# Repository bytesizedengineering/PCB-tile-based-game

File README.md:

# PCB Tile Based Board Game 

*Whoever completes the longest path wins! But beware of collisions!*  

## 🚀 Overview  
When Zach is not knee-deep in circuits and code, you can probably find him around a table covered in board games. For a long time now, a little project has been brewing in the back of his mind, designing a board game from the ground up, but not just any board game. Zach wants to create a tile-based game where the tiles electronically interact with each other the moment they snap together. It was featured on the Digkey [YouTube channel](https://www.youtube.com/@digikey) in [this video](https://youtu.be/TUmDfVxSnFg?si=vBeNglg9jUsEn66M).  

## 📂 Repository Structure  
```
📁 mechanical_design/   # 3D models (Fusion 360, STLs, STEP files)
📁 electrical_design/   # KiCad PCB and schematic files
📁 firmware/            # Arduino, ESP, or other firmware code
📁 docs/                # PDFs, images, and additional documentation
```

## 🔩 Mechanical Design  
You can access the latest Fusion 360 model here:  
[🔗 View 3D Model in Fusion 360](https://a360.co/4kI0F6f)

## 🏗️ Build Instructions  

### 🖨️ 3D Printing  
- **Recommended Material**: PLA/PETG  
- **Layer Height**: 0.2mm  
- **Supports**: No  

### 🔌 Electronics  
- **Microcontroller**: ATTiny3217  
- **Power Supply**: 5V  
- **PCB Fabrication**: Gerber files included in `electrical_design/` 

### 💾 Firmware Upload  
You can upload code to the ATtiny3217 using the [Adafruit UPDI Friend](https://learn.adafruit.com/adafruit-updi-friend). Here's a quick setup guide for the Arduino IDE:

🧰 What You Need
- Adafruit UPDI Friend
- Arduino IDE
- ATtiny3217 board
- USB-C cable
1. Install MegaTinyCore
2. Select the Board
3. Connect the UPDI Friend
4. Select the Serial Port
5. Upload Code

## 🛒 Bill of Materials (BOM)  
| Part            | Description                                 | Purchase Link                                     |
| --------------- | ------------------------------------------- | ------------------------------------------------- |
| Microcontroller | ATtiny3217                                  | [DigiKey](https://www.digikey.com/short/wtvwb0pv) |
| Connector       | Magnetic Connector Pair                     | [DigiKey](https://www.digikey.com/short/tv5t94mz) |
| Capacitor       | 0.1 µF Ceramic Capacitor                    |                                                   |
| LED             | Addressable Reverse-Mount RGB LED           | [DigiKey](https://www.digikey.com/short/zhvb3bff) |
| PCB             | Custom-designed                             |                                                   |

## 🎥 Video & More Info  
📺 Watch the full build video: [YouTube Video](https://youtu.be/TUmDfVxSnFg?si=vBeNglg9jUsEn66M)  

## 📝 License  
This project is licensed under the **GNU General Public License v3.0**.  
You can read the full text in the [`LICENSE`](LICENSE) file or at [gnu.org](https://www.gnu.org/licenses/gpl-3.0.html).  

## ❤️ Support  
- Found this helpful? Consider supporting me on [Patreon](https://www.patreon.com/ByteSizedEngineering) or [YouTube Memberships](https://www.youtube.com/@ByteSizedEngineering/join).  
- Follow me on [YouTube](https://www.youtube.com/@ByteSizedEngineering), [Instagram](https://www.instagram.com/bytesizedengineering/), and [GitHub](https://github.com/bytesizedengineering).

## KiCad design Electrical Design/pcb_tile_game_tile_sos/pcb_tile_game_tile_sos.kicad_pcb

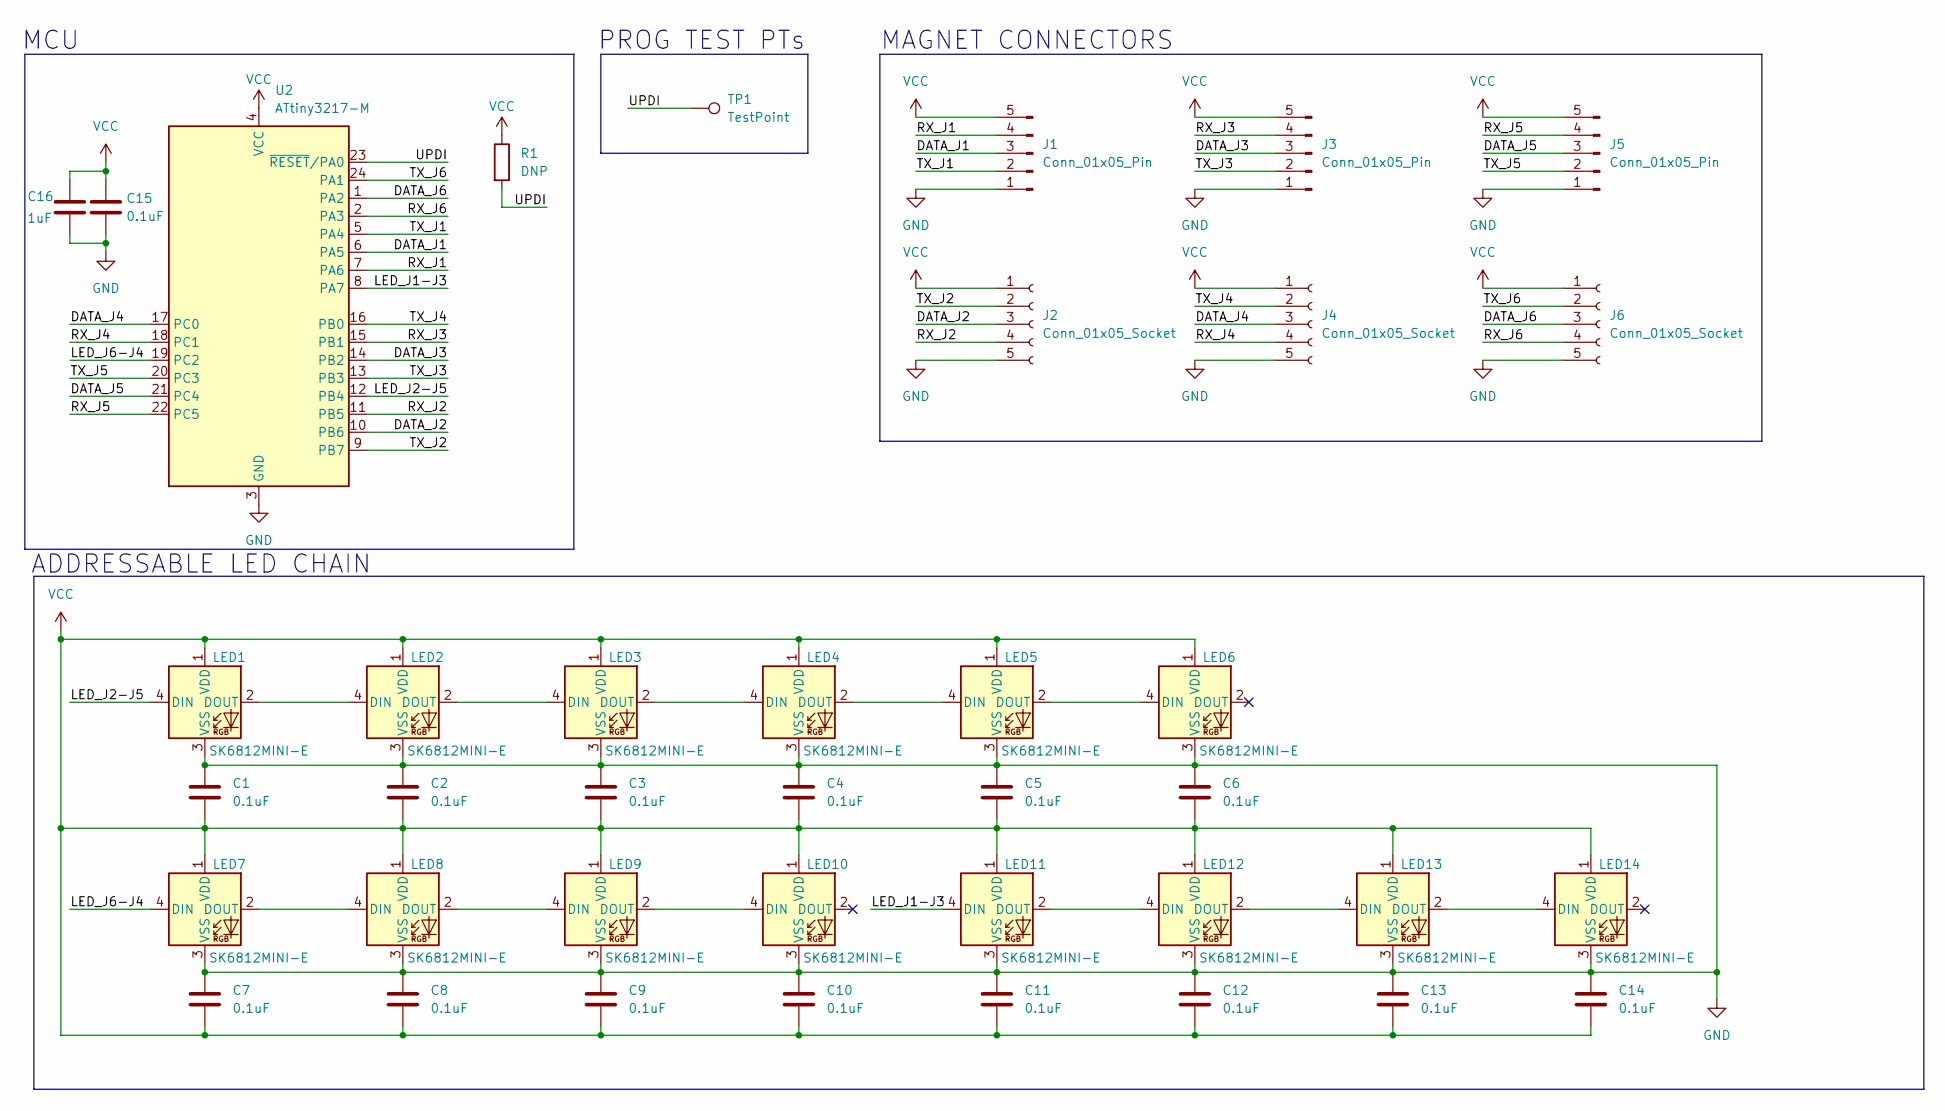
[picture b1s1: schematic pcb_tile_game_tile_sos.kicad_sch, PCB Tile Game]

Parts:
C1, C2, C3, C4, C5, C6, C7, C8, C9, C10, C11, C12, C13, C14, C15: 0.1uF; C_0603_1608Metric_Pad1.08x0.95mm_HandSolder
C16: 1uF; C_0603_1608Metric_Pad1.08x0.95mm_HandSolder
J1, J3, J5: Conn_01x05_Pin; PinHeader_1x05_P2.54mm_Vertical
J2, J4, J6: Conn_01x05_Socket; PinSocket_1x05_P2.54mm_Vertical
LED1, LED2, LED3, LED4, LED5, LED6, LED7, LED8, LED9, LED10, LED11, LED12, LED13, LED14: SK6812MINI-E; DigiKey Part Number 1528-4960-ND
R1: DNP; R_0603_1608Metric_Pad0.98x0.95mm_HandSolder
TP1: TestPoint; TestPoint_Pad_2.0x2.0mm
U2: ATtiny3217-M; QFN-24-1EP_4x4mm_P0.5mm_EP2.6x2.6mm

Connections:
/DATA_J1: J1.3, U2.6 (PA5)
/DATA_J2: J2.3, U2.10 (PB6)
/DATA_J3: J3.3, U2.14 (PB2)
/DATA_J4: J4.3, U2.17 (PC0)
/DATA_J5: J5.3, U2.21 (PC4)
/DATA_J6: J6.3, U2.1 (PA2)
/LED_J1-J6: LED11.4 (DIN), U2.8 (PA7)
/LED_J2-J5: LED1.4 (DIN), U2.12 (PB4)
/LED_J3-J4: LED7.4 (DIN), U2.19 (PC2)
/RX_J1: J1.4, U2.7 (PA6)
/RX_J2: J2.4, U2.11 (PB5)
/RX_J3: J3.4, U2.15 (PB1)
/RX_J4: J4.4, U2.18 (PC1)
/RX_J5: J5.4, U2.22 (PC5)
/RX_J6: J6.4, U2.2 (PA3)
/TX_J1: J1.2, U2.5 (PA4)
/TX_J2: J2.2, U2.9 (PB7)
/TX_J3: J3.2, U2.13 (PB3)
/TX_J4: J4.2, U2.16 (PB0)
/TX_J5: J5.2, U2.20 (PC3)
/TX_J6: J6.2, U2.24 (PA1)
/UPDI: R1.2, TP1.1, U2.23 (~RESET/PA0)
GND: C1.1, C2.1, C3.1, C4.1, C5.1, C6.1, C7.1, C8.1, C9.1, C10.1, C11.1, C12.1, C13.1, C14.1, C15.2, C16.2, J1.1, J2.5, J3.1, J4.5, J5.1, J6.5, LED1.3 (VSS), LED2.3 (VSS), LED3.3 (VSS), LED4.3 (VSS), LED5.3 (VSS), LED6.3 (VSS), LED7.3 (VSS), LED8.3 (VSS), LED9.3 (VSS), LED10.3 (VSS), LED11.3 (VSS), LED12.3 (VSS), LED13.3 (VSS), LED14.3 (VSS), U2.3 (GND), U2.25 (GND)
unnamed: LED1.2 (DOUT), LED2.4 (DIN)
unnamed: LED2.2 (DOUT), LED3.4 (DIN)
unnamed: LED3.2 (DOUT), LED4.4 (DIN)
unnamed: LED4.2 (DOUT), LED5.4 (DIN)
unnamed: LED5.2 (DOUT), LED6.4 (DIN)
unnamed: LED7.2 (DOUT), LED8.4 (DIN)
unnamed: LED8.2 (DOUT), LED9.4 (DIN)
unnamed: LED9.2 (DOUT), LED10.4 (DIN)
unnamed: LED11.2 (DOUT), LED12.4 (DIN)
unnamed: LED12.2 (DOUT), LED13.4 (DIN)
unnamed: LED13.2 (DOUT), LED14.4 (DIN)
VCC: C1.2, C2.2, C3.2, C4.2, C5.2, C6.2, C7.2, C8.2, C9.2, C10.2, C11.2, C12.2, C13.2, C14.2, C15.1, C16.1, J1.5, J2.1, J3.5, J4.1, J5.5, J6.1, LED1.1 (VDD), LED2.1 (VDD), LED3.1 (VDD), LED4.1 (VDD), LED5.1 (VDD), LED6.1 (VDD), LED7.1 (VDD), LED8.1 (VDD), LED9.1 (VDD), LED10.1 (VDD), LED11.1 (VDD), LED12.1 (VDD), LED13.1 (VDD), LED14.1 (VDD), R1.1, U2.4 (VCC)

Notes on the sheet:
PROG TEST PTs
MCU
ADDRESSABLE LED CHAIN
MAGNET CONNECTORS

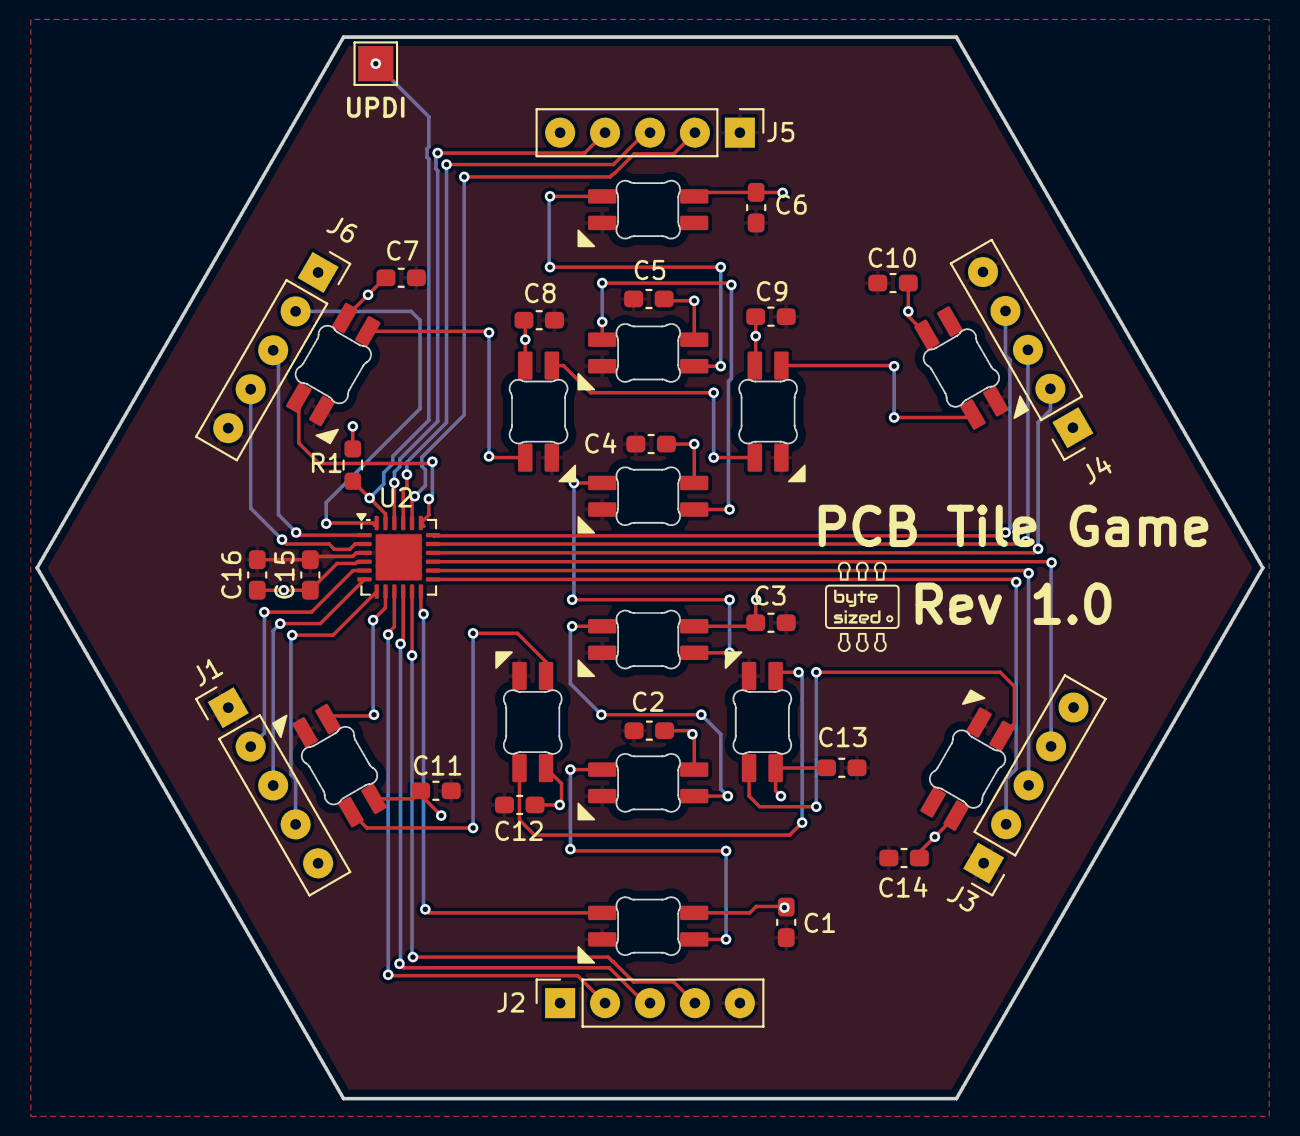
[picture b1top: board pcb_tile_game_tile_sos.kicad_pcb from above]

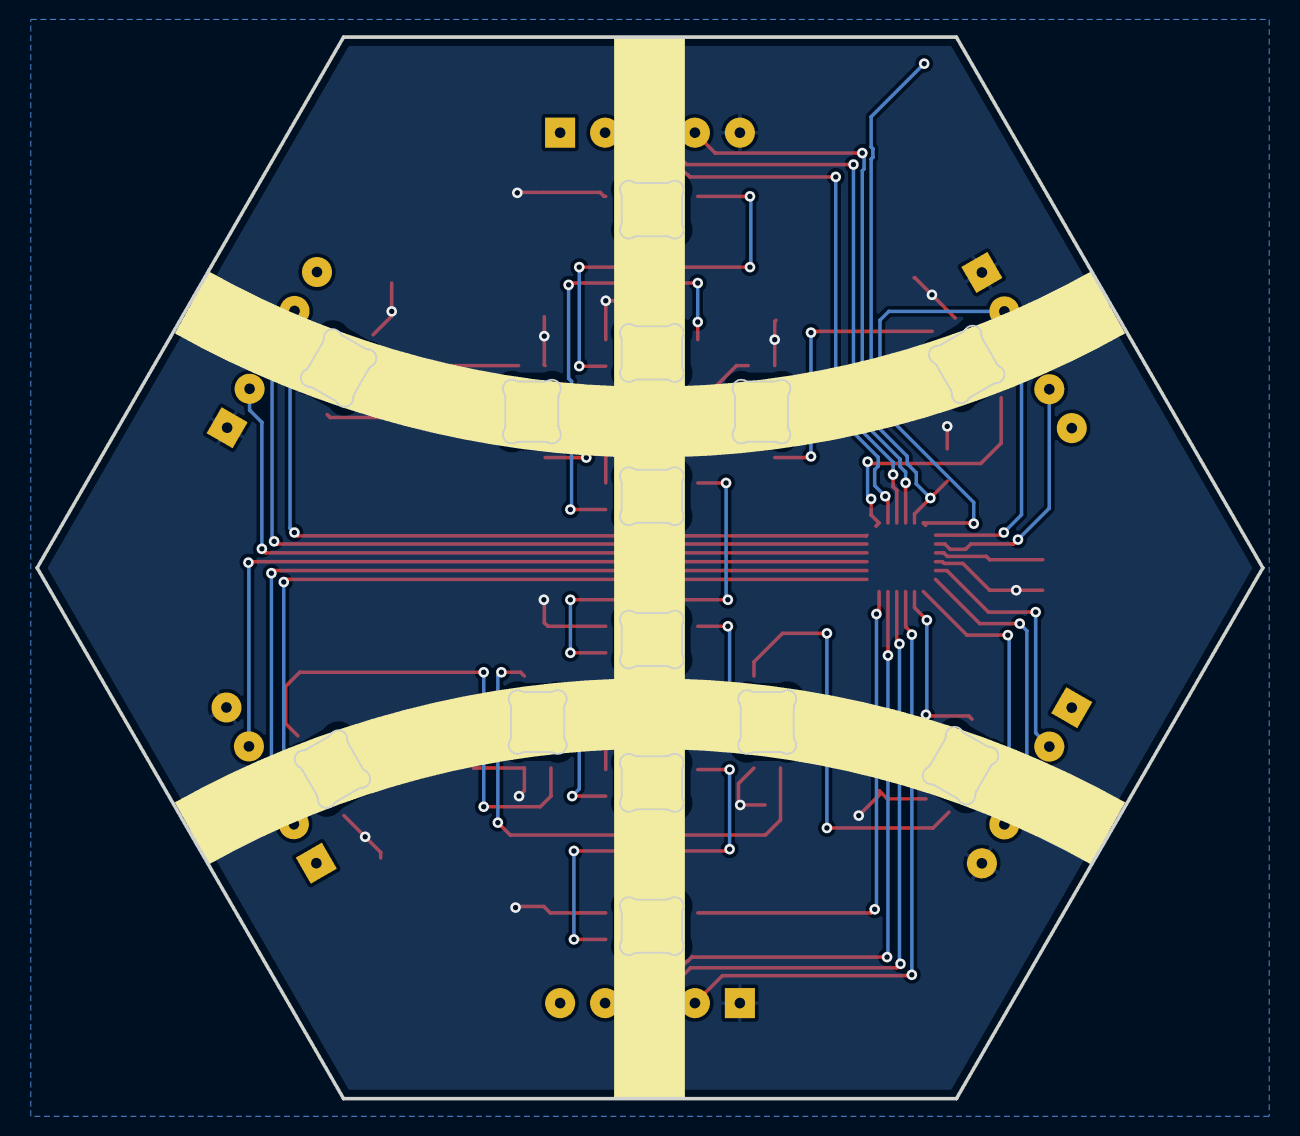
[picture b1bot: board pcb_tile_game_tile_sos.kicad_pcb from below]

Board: 2 copper layers, 69.3 x 60.0 mm, 39 parts (14 on the bottom side), 35 nets.

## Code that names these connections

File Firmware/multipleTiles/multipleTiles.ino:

#define RX_J1 PIN_PA6
#define TX_J1 PIN_PA4
#define DATA_J1 PIN_PA5

#define RX_J2 PIN_PB5
#define TX_J2 PIN_PB7
#define DATA_J2 PIN_PB6

#define RX_J3 PIN_PB1
#define TX_J3 PIN_PB3
#define DATA_J3 PIN_PB2

#define RX_J4 PIN_PC1
#define TX_J4 PIN_PB0
#define DATA_J4 PIN_PC0

#define RX_J5 PIN_PC5
#define TX_J5 PIN_PC3
#define DATA_J5 PIN_PC4

#define RX_J6 PIN_PA3
#define TX_J6 PIN_PA1
#define DATA_J6 PIN_PA2

#define LED_J2_J5 PIN_PB4
#define LED_J3_J4 PIN_PC2
#define LED_J1_J6 PIN_PA7

#include <SoftwareSerial.h>
#include <tinyNeoPixel.h>


// define SoftwareSerial objects
SoftwareSerial J1Serial (RX_J1, TX_J1);
SoftwareSerial J2Serial (RX_J2, TX_J2);
SoftwareSerial J3Serial (RX_J3, TX_J3);
SoftwareSerial J4Serial (RX_J4, TX_J4);
SoftwareSerial J5Serial (RX_J5, TX_J5);
SoftwareSerial J6Serial (RX_J6, TX_J6);

// define tinyNeoPixel objects
tinyNeoPixel pixels_J2_J5 = tinyNeoPixel(6, LED_J2_J5, NEO_GRB + NEO_KHZ800);
tinyNeoPixel pixels_J3_J4 = tinyNeoPixel(4, LED_J3_J4, NEO_GRB + NEO_KHZ800);
tinyNeoPixel pixels_J1_J6 = tinyNeoPixel(4, LED_J1_J6, NEO_GRB + NEO_KHZ800);

void setup() {
  // begin all serial instances
  Serial.begin(115200);
  J1Serial.begin(9600);
  J2Serial.begin(9600);
  J3Serial.begin(9600);
  J4Serial.begin(9600);
  J5Serial.begin(9600);
  J6Serial.begin(9600);

  // Initialize all tinyNeoPixel strands.
  pixels_J2_J5.begin(); pixels_J2_J5.clear();
  pixels_J3_J4.begin(); pixels_J3_J4.clear();
  pixels_J1_J6.begin(); pixels_J1_J6.clear();

}

void loop() {
  if (J1Serial.available() >= 3) {    
    byte red = J1Serial.read();
    byte green = J1Serial.read();
    byte blue = J1Serial.read();
    Serial.print("J1Serial received: "); Serial.print(red); Serial.print(green); Serial.println(blue);
    colorWipe("J1", red, green, blue);
  }
  Serial.println("looping");
}

void colorWipe(String side, byte redValue, byte greenValue, byte blueValue){
  if(side == "J1"){
    for (int i = 0; i < 4; i++) {
    pixels_J1_J6.setPixelColor(i, pixels_J1_J6.Color(redValue, greenValue, blueValue)); 
    pixels_J1_J6.show(); // This sends the updated pixel color to the hardware.
    delay(500); // Delay for a period of time (in milliseconds).
  }
  }
}

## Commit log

2025-02-20 updated 3D models and silkscreen
    Added magnetic connector models, LED models, changed path thickness, added title, revision, and logo to silkscreen.
2025-02-21 Updated pcb layout
    rerouted all traces, adjusted position of LEDs and silkscreen.
2025-03-28 Firmware, and capacitor
    Added firmware folder, and added additional capacitor in parallel to C15 in schematic. Footprint still needs to be added
2025-04-07 Create 5 variant tiles. Decrease mag connector hole size. Change path silkscreen to 4mm wide.
2025-04-07 Change PCB version to 1.0
2025-04-07 Create LICENSE
2025-04-15 created gerbers
2025-04-25 firmware added
    I wrote a unified code base for all pattern types. The unifiedTest code tests all LEDs and all connector pins as inputs
2025-04-26 updated firmware with comments and color mirroring
    This firmware has all basic functionality I set out to write. It reads color inputs, animates the 3 paths, and when animation is done, it mirrors color data on the path exit
2025-06-16 updated PCB design, mechanical design
